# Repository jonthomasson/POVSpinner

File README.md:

# POVSpinner
A simple POV (persistence of vision) fidget spinner. Made with an AtTiny85, 5 LED's, and 2 CR2032 batteries.

A few weeks ago a family member introduced me to the world of fidget spinners. At first I thought they were kinda silly, but after trying one, I started to see their appeal. It hit me that these would be really fun to build a POV (persistence of vision) display around. This project is a culmination of that idea. You can see the finished product in action here: https://www.youtube.com/watch?v=1BgokUmG97M 

Although the most popular fidget spinners seem to be the ones with 3 sides, for this project I decided to go with a 2 sided design. A 2 sided design would enable me to use 2 cr2032 batteries wired in parallel for power, one on either side of the spinner. This would help to balance out the spinner nicely as well as provide enough current to power a small micro and the leds. For the microcontroller, I went with the AtTiny85, since it had a small footprint, a wide operating voltage, and fairly low current draw. I'm using the trinket bootloader to load sketches into the board via the usb plug.

In my original design, I used the popular 608 size bearing. This by far was the bearing of choice it seemed for most fidget spinners. I found though that using this size, left almost no clearance on the sides of the board for traces running to the leds. Ultimately I decided to go instead with the R188 size bearing since, measuring only 12.7mm diameter, it gave me far more clearance to route traces around. I also was able to leave enough clearance around this bearing to hopefully add a cap to make spinning a little easier.

Finally, the ultimate goal of this project was to make something that could inspire fun and learning in this new generation of kids obsessed with fidget spinners. I did this through the use of a simple design, that is both low cost and easy to assemble. This project can be constructed in its entirety in a one off project for as little as $15 total, including the bearings and pcb. All of the components are within the range of anyone to solder. And the schematic and design are easy for anyone to understand.
![enter image description here](https://lh3.googleusercontent.com/DhNOqLcnItDuo_4iJxkey9anFaUFrb0ddoZT6aBiR9evClm_AYBNzVEmYPulBlhxkZ5F0HzZf8USn-Oaba-tvRUW2f26RHXr0ZZY7M68wkTW4eBEowTWm1YilmIVfi8iHBQSe3WZsqbQ8HsIK_B_Gx5_d8LAfAzL9G32k1ZT0BNbLnqP5z_AK59lP6lWOIZF0sos2zMfazeebM33W65sG-krZfV_TUBSA6Zb5zzz2ahZuokz029diugE4UWLXioPqCT0hP0HW1ibGR5ANN0v5VY58kcaZGH2PzBd3FSHQhWiSARxVtSGHpWVHd5jneaVidMeaFPLx4-RvemHsmrsusc5qVwqTvhs91gWdEjabqMJwCrjp3mItc6zM9olFMiIPqOjZFPV7rguPSyTsZM3JQV2UYWuxsDU0AvA6ZXtJ1jn_IkyUS59B75o749XTdhhhciiv453ezl28_-12i_rj5sswHuwHTHoUJL5eS99CCgSbqHjfacOzmijbIhgCu4UDaSEBqYiioIPvAMAW-v_CX7WVxJdjIcWLNiDNf-Owl6Ed2F-WKY0lOtcFgLFz2AO23rBnrBgrnAz_o-1bICzPigFwffIGYz_Kc6Xm4IOpumjnjKA2t1hD2ZOaJkj_04U7SlGKoQm-x79la2KrgtyDxItqlWOJOr4nw=w667-h888-no)

![enter image description here](https://lh3.googleusercontent.com/bpmZXRshKWY_OdYD_Kt2YicKdZAlTvVXNBgJA6td2XHRJgiZ3ofWQoVn10eOdQVJL2B-P29Dyr7ATuvkN6joMWVmaqQKLKum0x6HNuumbUMTG-wt7oL7T_7EQA7VCcBzKxEBSwDJUR6cZgD1WTrnYuZiJGE2PTgHFh-BVoChfHqBMX80PtWCEqrYn8nDAWuuoVQXNx0KrtBxYPSIfmA1YcdGvWze330QSJqTISdJTb_kGXB61h7jBFgwqJSsQXmbBlDi9PTR1a-ktpfKr108vbi9N9-dx_H22C2F0i8c2IH0O9bj9qjaQI__VALWmMF-AA-9cbXCs3t5nRBp2PkKARKo_qt9vhPap1HNayngJJg26BQUARaYvjfGhbRlGZsV1hmOxJ8drMRFkv6cqiE2lSYhSU2IultCqpbvPe5pw5s7U3q4UYpTMSoKG84IHNNoUOHoM_JgugRUICXM9hb9yCjHqq2xfNlvLWa8DxTRpkMwQ0TARM_XEV_ArprGf5H087rHniLuSmeD_yWus1PBRIDzcSW3lNLGlvNuLI6UtVtjBeCi25W4cDJAGTL82Qf1iaxncECHBsRkimoEmVJG3XgrxqN0U9ltwpZtgT7RlUN1kHuyP-krdMD7si1P7eL0TTSFSD8GL_ZEpBw9V3NK8hQbCYbW4rYZhg=w1579-h888-no)

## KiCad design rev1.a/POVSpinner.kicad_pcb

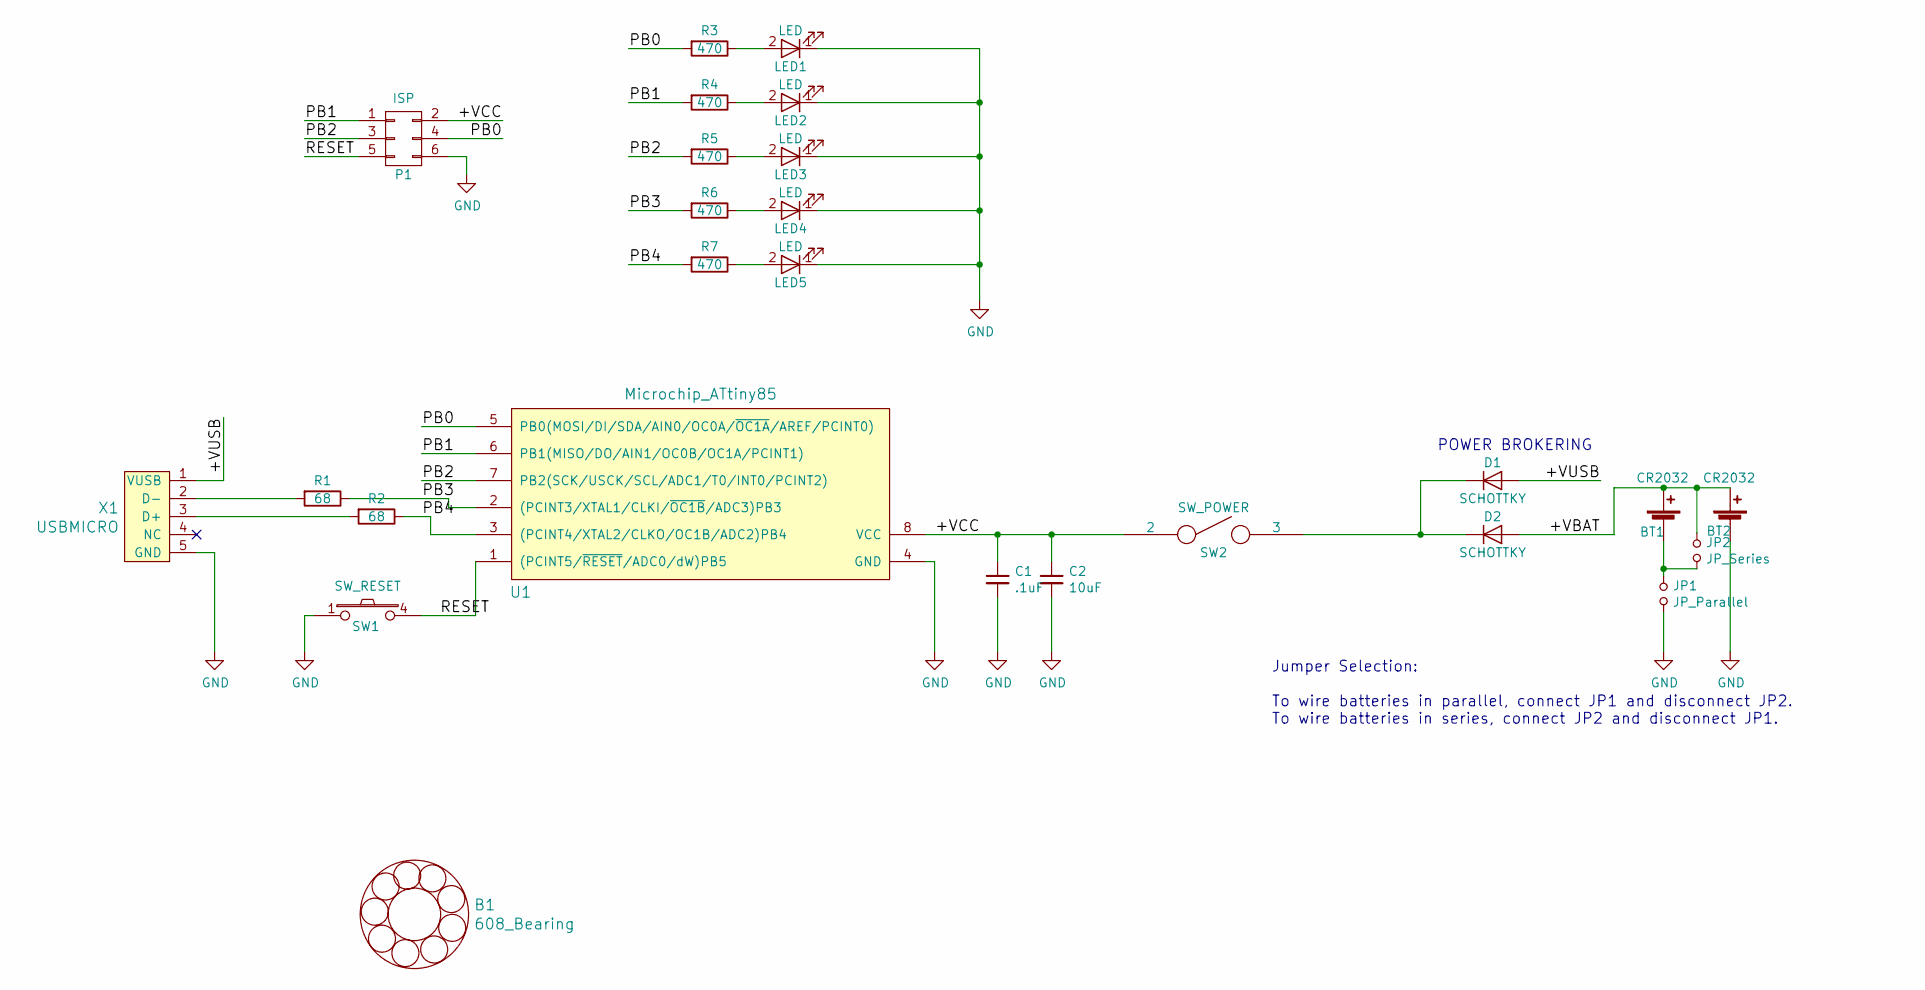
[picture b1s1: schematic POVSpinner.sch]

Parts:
B1: 608_Bearing
BT1, BT2: CR2032; BatteryHolder_MPD_BK_888
C1: .1uF; C_0805
C2: 10uF; C_0805
D1, D2: SCHOTTKY; SOD-523
JP1: JP_Parallel; SJ2
JP2: JP_Series; SJ2
LED1, LED2, LED3, LED4, LED5: LED; LED_0805
P1: ISP
R1, R2: 68; R_0805
R3, R4, R5, R6, R7: 470; R_0805
SW1: SW_RESET; SWITCH_PTS810
SW2: SW_POWER; SWITCH_CL_SB_12B
U1: Microchip_ATtiny85; SOIC-8_3.9x4.9mm_Pitch1.27mm
X1: USBMICRO; MICRO_USB_10118194

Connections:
/+VBAT: BT1.1 (+), BT2.1 (+), D2.2 (A), JP2.1
/+VCC: C1.1, C2.1, P1.2, SW2.2, U1.8 (VCC)
/+VUSB: D1.2 (A), X1.1 (VUSB)
/PB0: P1.4, R3.2, U1.5 (PB0(MOSI/DI/SDA/AIN0/OC0A/~OC1A~/AREF/P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)
/PB1: P1.1, R4.2, U1.6 (PB1(MISO/DO/AIN1/OC0B/OC1A/PCINT1))
/PB2: P1.3, R5.2, U1.7 (PB2(SCK/USCK/SCL/ADC1/T0/INT0/PCINT2))
/PB3: R1.1, R6.2, U1.2 ((PCINT3/XTAL1/CLKI/~OC1B~/ADC3)PB3)
/PB4: R2.1, R7.2, U1.3 ((PCINT4/XTAL2/CLKO/OC1B/ADC2)PB4)
/RESET: P1.5, SW1.4, U1.1 ((PCINT5/~RESET~/ADC0/dW)PB5)
GND: BT2.2 (-), C1.2, C2.2, JP1.2, LED1.1 (K), LED2.1 (K), LED3.1 (K), LED4.1 (K), LED5.1 (K), P1.6, SW1.1, U1.4 (GND), X1.5 (GND)
unnamed: BT1.2 (-), JP1.1, JP2.2
unnamed: D1.1 (K), D2.1 (K), SW2.3
unnamed: LED1.2 (A), R3.1
unnamed: LED2.2 (A), R4.1
unnamed: LED3.2 (A), R5.1
unnamed: LED4.2 (A), R6.1
unnamed: LED5.2 (A), R7.1
unnamed: R1.2, X1.2 (D-)
unnamed: R2.2, X1.3 (D+)

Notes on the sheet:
POWER BROKERING
Jumper Selection: To wire batteries in parallel, connect JP1 and disconnect JP2. To wire batteries in series, connect JP2 and disconnect JP1.

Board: 2 copper layers, 26 parts (2 on the bottom side), 19 nets, no tracks yet.

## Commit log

2017-06-15 added larger blocking diodes and fixed the isp connector pinout
2017-06-22 added new 5.3mm soic 8 footprint for AtTiny85
2018-02-09 added firmware
